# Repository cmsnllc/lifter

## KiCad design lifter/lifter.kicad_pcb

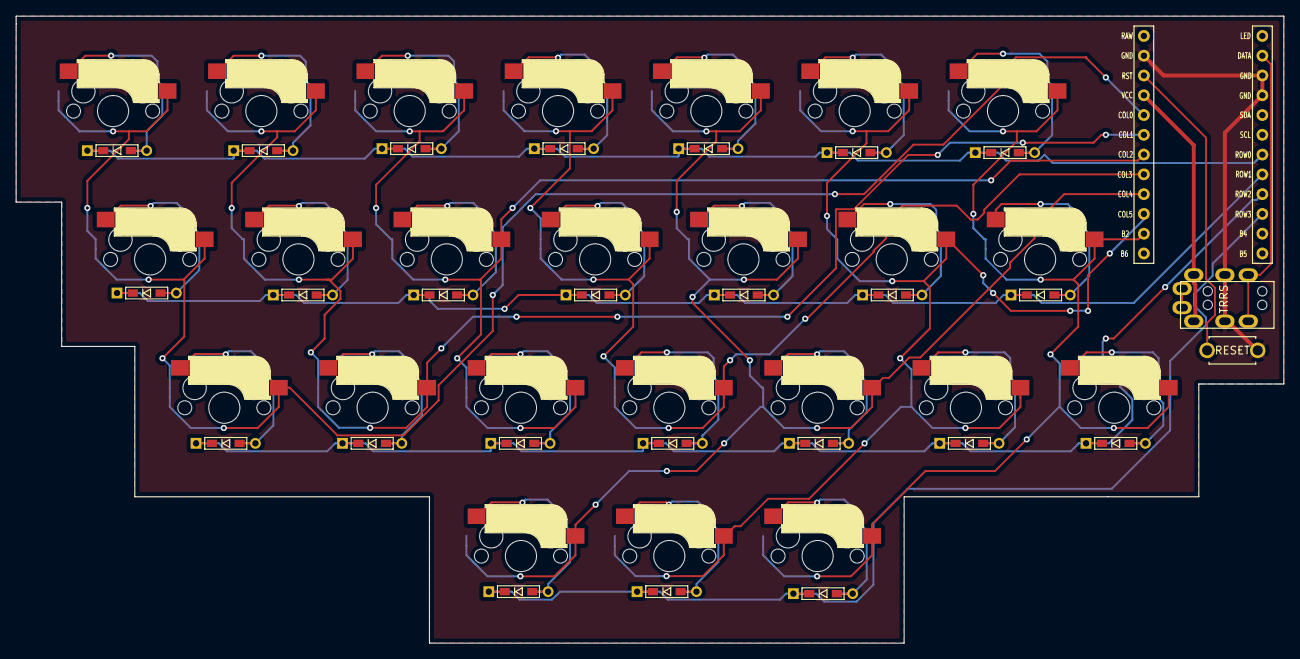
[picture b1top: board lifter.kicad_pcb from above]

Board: 2 copper layers, 162.8 x 80.5 mm, 51 parts (0 on the bottom side), 39 nets.

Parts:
D1, D2, D3, D4, D5, D6, D7, D8, D9, D10, D11, D12, D13, D14, D15, D16, D17, D18, D19, D20, D21, D22, D23, D24: D; D3_TH_SMD
J1: MJ-4PP-9
SW1, SW2, SW3, SW4, SW5, SW6, SW7, SW8, SW9, SW10, SW11, SW12, SW13, SW14, SW15, SW16, SW17, SW18, SW19, SW20, SW21, SW22, SW23, SW24: SW_PUSH; CherryMX_Hotswap
SW25: SW_PUSH; ResetSW
U1: ProMicro; ProMicro_v3

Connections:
GND: J1.C, SW25.2, U1.3, U1.4, U1.23
unnamed: D1.2, SW1.2
unnamed: D2.2, SW2.2
unnamed: D3.2, SW3.2
unnamed: D4.2, SW4.2
unnamed: D5.2, SW5.2
unnamed: D6.2, SW6.2
unnamed: D7.2, SW7.2
unnamed: D8.2, SW8.2
unnamed: D9.2, SW9.2
unnamed: D10.2, SW10.2
unnamed: D11.2, SW11.2
unnamed: D12.2, SW12.2
unnamed: D13.2, SW13.2
unnamed: D14.2, SW14.2
unnamed: D15.2, SW15.2
unnamed: D16.2, SW16.2
unnamed: D17.2, SW17.2
unnamed: D18.2, SW18.2
unnamed: D19.2, SW19.2
unnamed: D20.2, SW20.2
unnamed: D21.2, SW21.2
unnamed: D22.2, SW22.2
unnamed: D23.2, SW23.2
unnamed: D24.2, SW24.2
VCC: J1.D, U1.21
col0: SW1.1, SW8.1, SW15.1, U1.20
col1: SW2.1, SW9.1, SW16.1, U1.19
col2: SW3.1, SW10.1, SW17.1, U1.18
col3: SW4.1, SW11.1, SW18.1, U1.17
col4: SW5.1, SW12.1, SW19.1, SW22.1, U1.16
col5: SW6.1, SW13.1, SW20.1, SW23.1, U1.15
col6: SW7.1, SW14.1, SW21.1, SW24.1, U1.14
data: J1.B, U1.2
reset: SW25.1, U1.22
row0: D1.1, D2.1, D3.1, D4.1, D5.1, D6.1, D7.1, U1.7
row1: D8.1, D9.1, D10.1, D11.1, D12.1, D13.1, D14.1, U1.8
row2: D15.1, D16.1, D17.1, D18.1, D19.1, D20.1, D21.1, U1.9
row3: D22.1, D23.1, D24.1, U1.10

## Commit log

2018-12-01 Add layout
2018-12-03 Add prototype
